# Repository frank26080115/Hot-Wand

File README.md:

# Hot-Wand

This is a handcrafted Metcal RF soldering iron station. It is compact, and powered by USB-C, or a battery, or a DC power supply.

It is compatible with 13.56 MHz handpieces (Metcal, Thermaltronics, Hakko). If the handpiece uses 13.56 MHz and a F-type coaxial connector, then it is compatible.

The project's name, Hot-Wand, reflects how a RF soldering iron feels like magic, and justifies their typical multiple-hundreds-of-dollars price. The spirit of this project is not to lower the price, but to make it portable.

For the light-hearted story of this project, please see [my personal blog post](https://eleccelerator.com/hot-wand-the-rf-soldering-iron/)

The RF circuitry is a derivative of [SergeyMax's design](https://github.com/SergeyMax/SolderingStation), with modifications:

 * redrawn schematic for clarity
 * layout to fit in a Hammond MFG enclosure (or 3D printed enclosure)
 * removed AC power input, uses DC inputs (battery XT30 connector) or USB-PD (with negotiation for 28V)
 * uses a 128x32 OLED display
 * options for low power mode, automatic sleep
 * uses a STM32F042F6P6 microcontroller (more flash memory)
 * cooling fan, temperature sensors
 * internal glass fuse
 * substituted parts that are only available from Russia, or, are otherwise hard to get

I implemented a rather fancy GUI, fancier than what is available on a Metcal soldering station. The firmware features/supports:

 * persistent settings, edited through a setup menu
 * foreground and background power/thermal management
 * low battery warning/cutoff
 * user triggered sleep mode (basically, the power switch)
 * idle detection for automatic sleep
 * various fault detection
 * easter eggs! try and find them

Demo of the power modes:

A key aspect of my design is that it's **easy to build, and to prove it, I built 5 of these in my first batch, and they needed no rework**. All of the lessons and mistakes from the SergeyMax design are accounted for. The files are ready for PCBA assembly service upload and I've optimized the hand assembly to minimize tuning. I want my github repo to be a one-stop-shop of information for anybody who wants to build one.

Actually I built 10, there are 5 of each design, you can see why designing it in a way that doesn't annoy me during the build is important. These are going to be gifts to my BattleBots teammates and friends. The world is stressing everyone out, we could all use some cheering up right now. (can you guess what are our favorite tool brands?)

The circuit board was partially manufactured by a PCBA service, and there are some hand assembly still to be done afterwards. Some of the inductors has to be custom wound.

The USB-C connector is connected to a USB-PD negotiation IC, and the user can choose between using 28V or 20V depending on what USB brick they have. The user can also pick between 3A or 5A but this also depends on the USB cable. There are some tricks (firmware and electrical) being done to make sure the system does not overload the USB-PD host/cable.

The XT30 connector allows the user to connect a battery pack. The user can enable a battery chemistry mode, then features like automatic cell count and low battery cutoff becomes available (the user can also override the cutoff).

The RF power output is through a F-type connector, so it is compatible with most 13.56 MHz handpieces, such as Metcal, Thermaltronics, Hakko.

On paper, the buck converter that is actually powering the RF amplifier is set to 20V output with a 5A current limit. Thinking this means a 80W heat output is optimistic, I would expect somewhere between 50W to 80W of actual heating power, while using up to about 120W total from the upstream. Thus, the highest power setting is meant to be compatible with 140W USB-PD GaN chargers. It does technically work with a 65W USB-PD charger but the experience is a bit degraded.

The buck converter cannot boost the voltage from the input, so using any input voltage below about 22V would mean maximum power cannot be reached. The system cannot function at all below 14V. The DC input is rated for up to a 36V input. There is a glass fuse inside that limits the total system power draw to 7 amps.

While this is a DIY project and not a commercial product, it is a difficult project as it requires hand-wound inductors and tuning the inductor coils. This project is a learning experience, as I had to study the (translated from Russian) blog post made by SergeyMax in detail. See my page on the [design study](./doc/design-study/design-study.md).

## Hot-Wand Lite

In the same spirit, a compact RF soldering iron station. Compatible with 470 kHz handpieces. This is the inexpensive version. It is a derivative of the [Radio Thermal](https://radiothermal.com/) soldering iron station, but with modifications

 * layout to fit in a 3D printed enclosure (but compatible with the Hammond enclosure)
 * uses battery XT30 connector or USB-PD for input
 * uses some sort of Seeed Studio XIAO microcontroller module
 * user selectable power levels via externally pluggable jumpers
 * internal glass fuse

Physically, Hot-Wand and Hot-Wand-Lite uses the same PCB dimensions. The power input stage are almost identical. The RF output connector is a SMA connector this time. [Radio Thermal](https://radiothermal.com/) (the inspiration for this) has instructions on how to build a cheap handpiece.

This cost saving design has way less fault protection.

While this is a DIY project and not a commercial product, it is a difficult project as it requires hand-wound inductors and tuning the inductor coils. Regarding how this is copying a lot of the [Radio Thermal](https://radiothermal.com/) design, I am copying it almost verbatim, as they do not use anything weird from Russia, and the RF design education I've already gotten from the much more complicated 13.56 MHz version of Hot-Wand.

## What is a RF soldering iron anyways?

An RF soldering iron sends high-frequency electromagnetic energy into a purpose-built tip cartridge, where a thin magnetic heating layer produces heat very close to the working end; in Curie-regulated cartridges, that layer also changes how strongly it absorbs energy as it approaches its designed temperature. Compared with a conventional iron whose resistive heater must heat a larger structure and conduct that heat to the tip, the shorter thermal path and low effective thermal lag let an RF tip respond immediately when a solder joint draws heat and recover its temperature quickly afterward. That fast, load-responsive delivery is why a nominally 50 W RF iron can feel more capable than a nominally 100 W resistive iron: the wattage rating describes available electrical power, while the user's experience is dominated by how quickly and efficiently that power reaches the joint and restores the tip temperature.

The RF soldering iron's station unit does not feature a temperature setting or even have the ability to detect the iron's temperature. When you buy the iron cartridge (which is the tip and stem), it is specific to one temperature. It will always be on target (within the manufacture's tolerance) because of the Curie-point behavior of the magnetic alloy built into the cartridge. Below its designed temperature, the alloy is magnetic and the skin effect concentrates RF current in its thin, relatively high-resistance outer layer, producing heat right at the tip. At the Curie point the alloy loses its magnetic properties, the skin effect collapses, and the current moves into the low-resistance copper core, so heating drops sharply. When a solder joint cools the tip, the alloy becomes magnetic again and full heating immediately resumes. The temperature feedback mechanism is therefore inside the heater material itself, directly at the working tip, instead of being a sensor-and-controller loop back in the station.

## Project Ethos

I've always liked the Metcal MX-5200 I have access to at work. I'm also a robot combat competitor, both in insect weight classes and also a part of a heavyweight battlebots team. Thus, I travel with my tools a lot, sometimes even flying to NHRL from California. And while I like my [iFixit soldering iron](https://eleccelerator.com/review-ifixit-soldering-iron/) for it's portability, I thought it'd be cool to have a portable RF soldering iron.

While designing this project, the cost started to balloon. At one point it was decided to drop the pretense that DIY is cheaper, and instead, build something I would rather own even more than the actual (gigantic) MX-5200.

I also wanted to design and document this project in a way that makes it way more friendly for a DIY builder to actually build. To prove myself, the first batch was a batch of 5 and they all worked flawlessly with minimal tuning and zero rework.

Undertaking this project is not cheap, it requires a considerable amount of skill and for you to already have access to soldering equipment. You have been warned. If you need a good soldering iron for a reasonable cost, a Hakko FX-888DX or a iFixit Soldering Iron are still a good bets.

## Design Study

Please see [my full design study (click here)](doc/design-study/design-study.md). This includes:

 * Dissection of SergeyMax's design
 * Analyzes other DIY builder's notes as they build SergeyMax's design
 * Analyzes SergeyMax's follow-up video (that's in Russian)
 * My additional design choices, justifications, calculations
 * and more

See my [post-build report](doc/post-build-report.md) with findings and observations that I've made after completing the project

Please explore the [documentation directory itself](doc), as I might've written something but forgot to link it.

## Files and Build Guides

 * [Electrical Design Files](electrical)
 * [Files for Mechanical Parts](mechanical)
 * [DIY build guide for the Hot Wand (13.56 MHz version)](doc/build-guide-13mhz/build-guide.md)
 * [DIY build guide for the Hot Wand Lite (470 kHz version)](doc/build-guide-lite-470khz/build-guide-lite.md)
 * [Operation Instructions for the Hot Wand (13.56 MHz version)](doc/operating-instructions.md)
 * [Operation Instructions for the Hot Wand Lite (470 kHz version)](doc/operating-instructions-for-lite.md)
 * [DIY build guide for the Folding Iron Stand](doc/build-guide-iron-stand.md)
 * [Interactive Circuit Deep Dive for the Hot Wand (13.56 MHz version)](https://eleccelerator.com/hot-wand-deep-dive/electrical-deep-dive-13mhz.html)
 * [Interactive Circuit Deep Dive for the Hot Wand Lite (470 kHz version)](https://eleccelerator.com/hot-wand-deep-dive/electrical-deep-dive-lite-470khz.html)

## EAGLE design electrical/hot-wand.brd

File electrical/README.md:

This directory contains electrical design files for the Hot Wand project

The main `hot-wand` project is the 13.56 MHz version, while the `hot-wand-lite` is the 470 kHz version meant to be less expensive.

The schematic and PCB are designed with CadSoft EAGLE 7. PDF versions of the schematic and image previews of the PCB are provided for convenience.

 * [Interactive Circuit Deep Dive for the Hot Wand (13.56 MHz version)](https://eleccelerator.com/hot-wand-deep-dive/electrical-deep-dive-13mhz.html)
 * [Interactive Circuit Deep Dive for the Hot Wand Lite (470 kHz version)](https://eleccelerator.com/hot-wand-deep-dive/electrical-deep-dive-lite-470khz.html)

The `mfg` directory will contain the BOM and gerber files, along with some helpers that aid in generating these files.

The BOM, CPL files, and the design rules, are all meant for use with JLCPCB's PCBA service.

## Release Procedure

0. Run a DRU check, and also run `drill_sizes_report.bat` to catch stray drill sizes
1. Edit the symbol and footprint for the version to reflect the latest version designation
2. Generate the schematic preview PDF file using `eagle_schematic_preview.py`
3. Generate the gerber files using `generate_gerbers.bat` (this also generates the gerber preview)
4. Generate the BOM and CPL files using `generate_bom_cpl.bat`

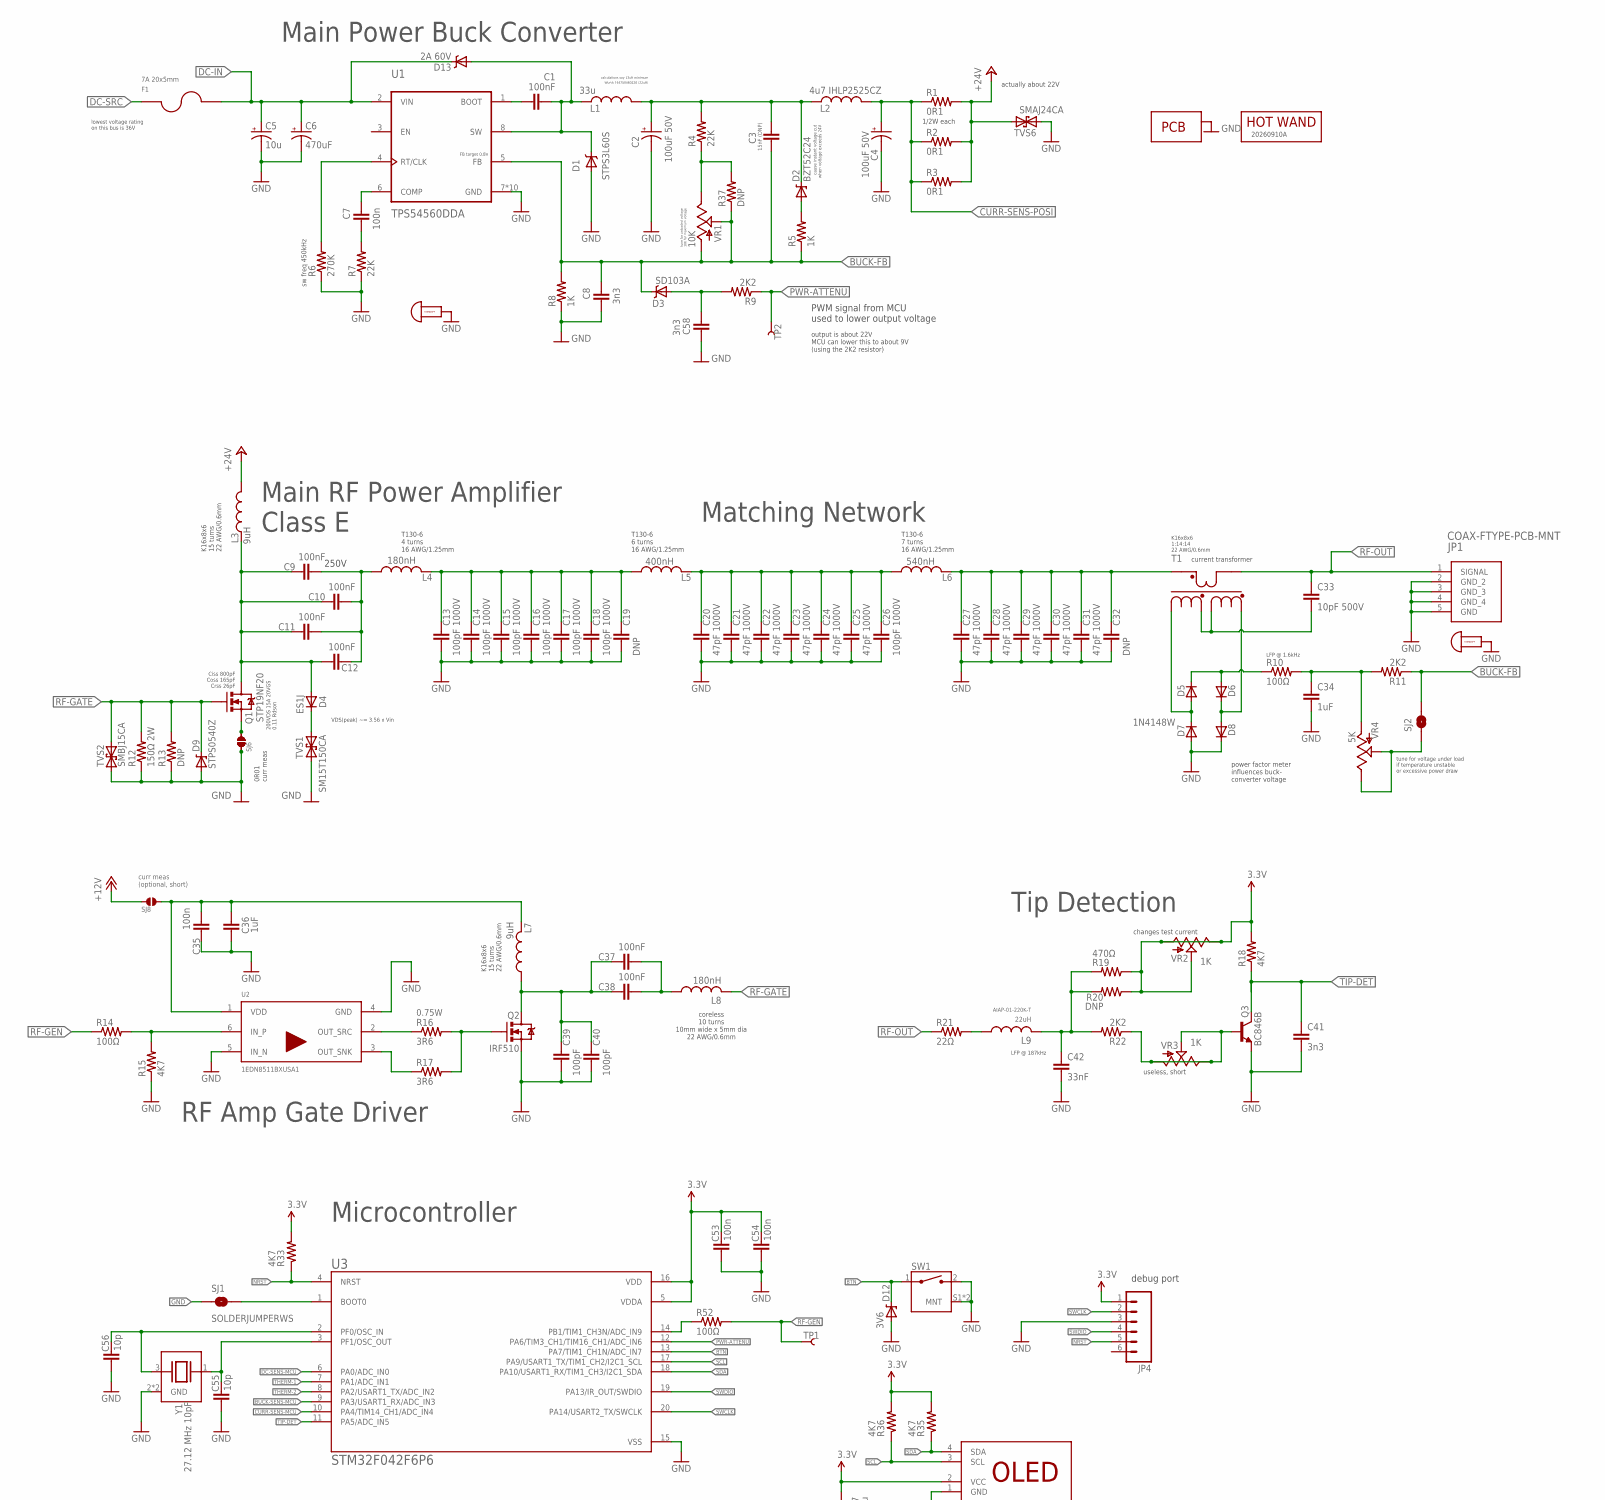
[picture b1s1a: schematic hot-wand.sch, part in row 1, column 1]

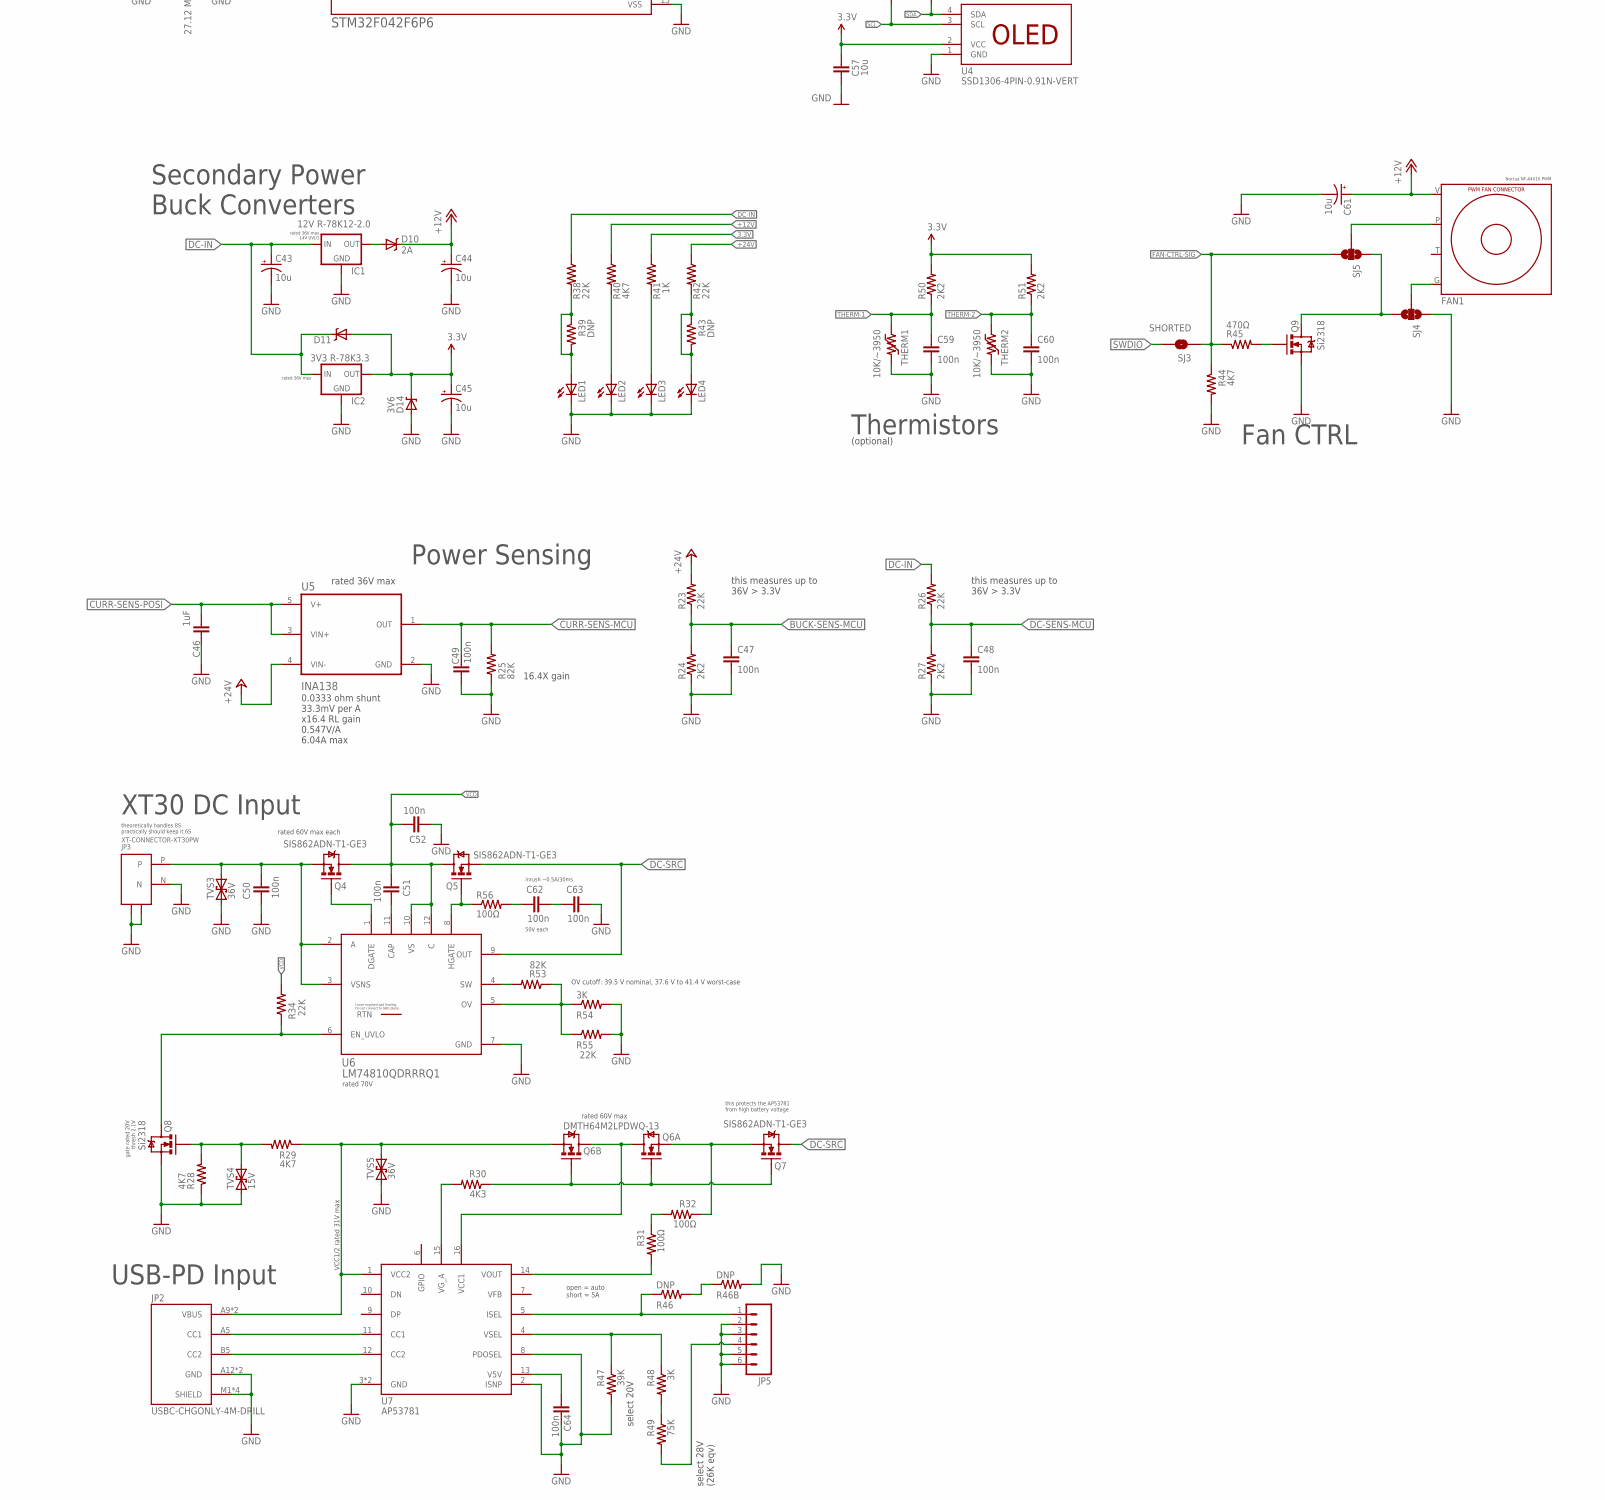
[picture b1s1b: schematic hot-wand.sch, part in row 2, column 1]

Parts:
C1: 100nF; 0603-CAP; JLCPARTNUM C14663
C2: 100uF 50V; CPOL-RADIAL-COMBO-10MM; PARTNUM EEU-FR1H101B;EEU-FR1J101B; JLC-DNP 1
C3: 15nF (DNP); 0805; JLC-DNP 1
C4: 100uF 50V; CPOL-RADIAL-COMBO-10MM; JLC-DNP 1
C5, C43, C61: 10u; EIA3216-KIT; PARTNUM MLASU31LBB5106KTNA01;GRT31CR61H106KE01K; JLCPARTNUM C13585
C6: 470uF; CPOL-RADIAL-1000UF-25V; PARTNUM UHW1H471MPD;EEU-FR1H471;EEU-FR1H471B; JLC-DNP 1
C7, C35, C48, C49, C50, C51, C52, C53, C54, C59, C60, C62, C63, C64: 100n; 0603-CAP; JLCPARTNUM C14663
C8, C41, C58: 3n3; 0603-CAP; JLCPARTNUM C1613
C9, C10, C11, C12, C37, C38: 100nF; 0805-L; PARTNUM CHV0805N250104KXT;MBASQ21GAB7104KTCA01;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; JLCPARTNUM C5182461
C13: 100pF 1000V; 0805-L; PARTNUM QCCT102Q101J1GV001E; JLCPARTNUM C6958299
C14, C15, C16, C17, C18, C26: 100pF 1000V; 0805-L; JLCPARTNUM C6958299
C19: DNP; 0805-L; JLCPARTNUM C6958299
C20: 47pF 1000V; 0805-L; PARTNUM QCCT102Q470J1GV001E; JLCPARTNUM C6366545
C21, C22, C23, C24, C25, C27, C28, C29, C30, C31: 47pF 1000V; 0805-L; JLCPARTNUM C6366545
C32: DNP; 0805-L; JLC-DNP 1
C33: 10pF 500V; 0805-L; PARTNUM QCCT102Q100J1GV001E; JLCPARTNUM C6629873
C34, C36, C46: 1uF; 0603-CAP; JLCPARTNUM C15849
C39, C40: 100pF; 0805-L; JLCPARTNUM C6958299
C42: 33nF; 0603-CAP; JLCPARTNUM C21117
C44: 10u; EIA3216-KIT; PARTNUM TAJA106K016TNJ;T491A106K016AT; JLCPARTNUM C13585
C45: 10u; EIA3216; PARTNUM TAJA106K016TNJ;T491A106K016AT; JLCPARTNUM C13585
C47: 100n; 0603-CAP
C55, C56: 10p; 0603-CAP; JLCPARTNUM C1634
C57: 10u; 1206; JLCPARTNUM C13585
D1: STPS3L60S; SMC; JLCPARTNUM C2971007
D2: BZT52C24; SOD123FL; JLCPARTNUM C2109
D3: SD103A; SOD-323; JLCPARTNUM C7420360
D4: ES1J; SMA-DIODE; JLCPARTNUM C64879
D5, D6, D8: 4148; SOD123FL; JLCPARTNUM C84367
D7: 1N4148W; SOD123FL; JLCPARTNUM C84367
D9: STPS0540Z; SOD123FL; JLCPARTNUM C181835
D10: 2A; SMA-DIODE; PARTNUM VSSAF5N50;SL36A; JLCPARTNUM C698873
D11: DIODE-SCHOTTKY_; SMA-DIODE; JLCPARTNUM C698873
D12, D14: 3V6; SOD-323; PARTNUM ESDLC3V3D3B-TP;CDSOD323-T03SC;SD03LCC; JLCPARTNUM C840638
D13: 2A 60V; SOD123FL; PARTNUM STPS2L60ZFY; JLCPARTNUM C53340922
F1: 7A 20x5mm; FUSE_5MM; PARTNUM Keystone 3518P; JLC-DNP 1
FAN1: FAN-CONN-X4-CONN-X4; FAN-CONN-X4
IC1: 12V R-78K12-2.0; TO220-BUCK-12V; JLC-DNP 1
IC2: 3V3 R-78K3.3; TO220-BUCK-3.3V; JLC-DNP 1
JP1: COAX-FTYPE-PCB-MNT; CONN_73330-0030_MOL; JLC-DNP 1
JP2: USBC-CHGONLY-4M-DRILL; SAMESKY_UJC-H-G-SMT-2-P6-TR-DRILL; JLC-DNP 1
JP3: XT-CONNECTOR-XT30PW; XT30PW; JLC-DNP 1
JP4: M06LOCK; 1X06_LOCK; JLC-DNP 1
JP5: M06LOCK; 1X06_LOCK
L1: 33u; IND_RADIAL_D12.7_COMBO; PARTNUM Wurth 744750460220 (22uH); JLC-DNP 1
L2: 4u7 IHLP2525CZ; IND_IHLP-2525CZ_VIS-M; PARTNUM IHLP2525CZER4R7M11; JLCPARTNUM C845027
L3, L7: 9uH; IND_K16X8X6_X2; JLC-DNP 1
L4: 180nH; IND_T130-6_X2; JLC-DNP 1
L5: 400nH; IND_T130-6_X2; JLC-DNP 1
L6: 540nH; IND_T130-6_X2; JLC-DNP 1
L8: 180nH; IND-10X6MM; JLC-DNP 1
L9: 22uH; TFI0410; PARTNUM AIAP-01-220K-T; JLC-DNP 1
LED1, LED2, LED3, LED4: LED; LED-0603; JLC-DNP 1
PCB1: PCB-OUTLINE; JLC-DNP 1
PCB2: PCB-ART-VERSION; JLC-DNP 1
Q1: STP19NF20; TO220V-REAR; JLC-DNP 1
Q2: IRF510; TO220V-REAR; JLC-DNP 1
Q3: BC846B; SOT23-3; JLCPARTNUM C181138
Q4, Q5, Q7: SIS862ADN-T1-GE3; POWERPAK-1212-8; JLC-DNP 1
Q6: DMTH64M2LPDWQ-13; POWERPAK-SO8-X2; JLC-DNP 1
Q8: Si2318; SOT23-3; PARTNUM 2N7002K;SSM3K388R,LF;Si2318CDS-T1-GE3;P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; JLCPARTNUM C14498;C547263;C5224211;C54347659
Q9: Si2318; SOT23-3; PARTNUM G3404;MMFTN3404A;PJA3404A;Si2318CDS-T1-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; JLCPARTNUM C14498;C547263;C96615
R1, R2, R3: 0R1; 1206; PARTNUM KDV12DR100ET;VMK-R033-1.0-U; JLCPARTNUM C188071
R4, R7, R23, R26, R34, R38, R42, R55: 22K; 0603-RES; JLCPARTNUM C31850
R5, R8, R41: 1K; 0603-RES; JLCPARTNUM C21190
R6: 270K; 0603-RES; JLCPARTNUM C137755
R9, R11, R22, R24, R27, R50, R51: 2K2; 0603-RES; JLCPARTNUM C4190
R10, R14, R52: 100Ω; 0603-RES; JLCPARTNUM C22775
R12: 150Ω 2W; R2512; PARTNUM CRGP2512F150R; JLCPARTNUM C175287
R13: DNP; R2512; PARTNUM CRGP2512F150R; JLC-DNP 1
R15, R18, R28, R29, R33, R35, R36, R40, R44: 4K7; 0603-RES; JLCPARTNUM C23162
R16, R17: 3R6; 1206; JLCPARTNUM C6301221
R19, R45: 470Ω; 0603-RES; JLCPARTNUM C23179
R20: DNP; 0805; JLC-DNP 1
R21: 22Ω; R2512; JLCPARTNUM C5204054
R25, R53: 82K; 0603-RES; JLCPARTNUM C23254
R30: 4K3; 0603-RES; JLCPARTNUM C23159
R31, R32, R56: 100Ω; 0805; JLCPARTNUM C441975
R37, R46, R46B: DNP; 0603-RES; JLC-DNP 1
R39, R43: DNP; 0603-RES
R47: 39K; 0603-RES; JLCPARTNUM C23153
R48, R54: 3K; 0603-RES; JLCPARTNUM C4211
R49: 75K; 0603-RES; JLCPARTNUM C23242
SJ1: SOLDERJUMPERWS; SJ_2S-WS; JLC-DNP 1
SJ2: SOLDERJUMPERNO; SJ_2S-NO; JLC-DNP 1
SJ3: SHORTED; SJ_2S-WS; JLC-DNP 1
SJ4, SJ5: SOLDERJUMPER_2WAYS; SJ_3
SJ6, SJ7, SJ8: SJ-SMALL-1206-SJ; 1206-SJ
STANDOFF1, STANDOFF2: STANDOFF-M2.5-4.5MMHEX
SW1: SW-TACT-SIDE; SW_1-1825027-1; PARTNUM MJTP1236D;TL1105JAF160R1RBLK; JLC-DNP 1
T1: XFORMER-1:14:14; XFORMER-K16X8X6-1:14:14; JLC-DNP 1
THERM1, THERM2: 10K/~3950; 1X02-2MM; PARTNUM B57891M0103K000; JLC-DNP 1
TP1, TP2: TEST-POINT-SQ-2MM; PAD-SQ-2MM
TVS1: SM15T150CA; SMC; JLCPARTNUM C133715
TVS2: SMBJ15CA; SMA-DIODE; JLCPARTNUM C78809
TVS3, TVS5: 36V; SMA; PARTNUM SMAJ36CA; JLCPARTNUM C134984
TVS4: 15V; SOD-323; PARTNUM SD15C-01FTG;CDSOD323-T15SC;TSD15CDYFR; JLCPARTNUM C2987151
TVS6: SMAJ24CA; SMA; JLCPARTNUM C148223
U1: TPS54560DDA; VREG_LM5017MR/NOPB; JLCPARTNUM C31966
U2: 1EDN8511BXUSA1; SOT95P280X145-6N-7-V; JLCPARTNUM C3655509
U3: STM32F042F6P6; SOP65P640X120-20N; JLCPARTNUM C2969989
U4: SSD1306-4PIN-0.91N-VERT; OLED-0.91IN-VERT; JLC-DNP 1
U5: INA138; SOT95P280X145-5N; JLCPARTNUM C47914
U6: LM74810QDRRRQ1; DRR0012E-MFG; JLCPARTNUM C3215601
U7: AP53781; QFN3030-16; JLCPARTNUM C52730979
VR1: 10K; TRIM_35WR1KLFTR_V2; PARTNUM TC33X-2-103E; JLC-DNP 1
VR2, VR3: 1K; TRIM_35WR1KLFTR_V3; PARTNUM TC33X-2-102E; JLC-DNP 1
VR4: 5K; TRIM_35WR1KLFTR_V2; PARTNUM TC33X-2-502; JLC-DNP 1
Y1: 27.12 MHz 10pF; XTAL-4SMD-3.2X2.5-V2; JLCPARTNUM C1986817

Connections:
3.3V: C45.A (+), C53.1, C54.1, C57.2, D11.A, D14.1 (C), IC2.3 (OUT), JP4.1, R18.2, R19.1, R20.1, R33.2, R35.2, R36.2, R41.1, R50.2, R51.2, U3.5 (VDDA), U3.16 (VDD), U4.2 (VCC), VR2.1 (A), VR2.2 (S), VR2.3 (E)
12V-2: D10.A, IC1.3 (OUT)
12V-FOR-GATE-DRIVER: C35.2, C36.2, L7.2, SJ8.2, U2.1 (VDD)
+12V: C44.A (+), C61.A (+), D10.C, FAN1.V, R40.1, SJ8.1
+24V: L3.2, R1.2, R2.2, R3.2, R23.2, R42.1, TVS6.C (2), U5.4 (VIN-)
BTN: D12.1 (C), SW1.1, U3.13 (PA7/TIM1_CH1N/ADC_IN7)
BUCK-1ST-STAGE: C2.1 (+), C2.1B (+), C3.2, D2.C, L1.2, L1.2B (2), L2.1, R4.2
BUCK-FB: C3.1, C8.2, D3.1 (C), R5.1, R8.2, R11.1, R37.1, SJ2.2, U1.5 (FB), VR1.1 (A), VR1.2 (S)
BUCK-SENS-MCU: C47.1, R23.1, R24.2, U3.9 (PA3/USART1_RX/ADC_IN3)
BUCK-SWITCH-NODE: C1.2, D1.C, D13.A, L1.1, L1.1B (1), U1.8 (SW)
CURR-SENS-MCU: C49.1, R25.2, U3.10 (PA4/TIM14_CH1/ADC_IN4), U5.1 (OUT)
CURR-SENS-POSI: C4.1 (+), C4.1B (+), C46.2, L2.2, R1.1, R2.1, R3.1, U5.3 (VIN+), U5.5 (V+)
DC-IN: C5.A (+), C6.1 (+), C43.A (+), D11.C, D13.C, F1.3 (2), F1.4 (2), IC1.1 (IN), IC2.1 (IN), R26.2, R38.1, U1.2 (VIN)
DC-SENS-MCU: C48.1, R26.1, R27.2, U3.6 (PA0/ADC_IN0)
DC-SRC: F1.1, F1.2 (1), Q5.1 (S), Q5.2 (S), Q5.3 (S), Q7.5 (D), Q7.6 (D), Q7.7 (D), Q7.8 (D), Q7.9 (D), U6.9 (OUT)
FAN-CTRL-SIG: R44.1, R45.1, SJ3.1, SJ5.3
GND: C2.2 (-), C2.2B (-), C4.2 (-), C4.2B (-), C5.C (-), C6.2 (-), C8.1, C13.2, C14.2, C15.2, C16.2, C17.2, C18.2, C19.2, C20.2, C21.2, C22.2, C23.2, C24.2, C25.2, C26.2, C27.2, C28.2, C29.2, C30.2, C31.2, C32.2, C34.2, C35.1, C36.1, C39.2, C40.2, C41.2, C42.2, C43.C (-), C44.C (-), C45.C (-), C46.1, C47.2, C48.2, C49.2, C50.2, C52.2, C53.2, C54.2, C55.2, C56.2, C57.1, C58.1, C59.2, C60.2, C61.C (-), C63.1, C64.1, D1.A, D7.A, D8.C, D9.A, D12.2 (A), D14.2 (A), IC1.2 (GND), IC2.2 (GND), JP1.2 (GND_2), JP1.3 (GND_3), JP1.4 (GND_4), JP1.5 (GND), JP2.A12 (GND), JP2.B12 (GND), JP2.M1 (SHIELD), JP2.M2 (SHIELD), JP2.M3 (SHIELD), JP2.M4 (SHIELD), JP3.M1, JP3.M2, JP3.N, JP4.3, JP5.2, JP5.3, JP5.5, JP5.6, LED1.C, LED2.C, LED3.C, LED4.C, PCB1.1, PCB1.2, PCB1.3, PCB1.4, Q2.3 (S), Q3.2 (E), Q8.2 (S), Q9.2 (S), R6.1, R7.1, R8.1, R12.1, R13.1, R15.1, R24.1, R25.1, R27.1, R28.1, R44.2, R46B.2, R47.2, R54.2, R55.2, SJ1.1, SJ4.1, SJ6.1, SJ7.1, STANDOFF1.1, STANDOFF1.2, STANDOFF2.1, STANDOFF2.2, SW1.2, SW1.S1 (MNT), SW1.S2 (MNT), THERM1.2, THERM2.2, TVS1.A (1), TVS2.A (1), TVS3.A (1), TVS4.2 (1), TVS5.A (1), TVS6.A (1), U1.7 (GND), U1.9 (GND), U1.10 (GND), U1.11 (GND), U1.12 (GND), U1.13 (GND), U1.14 (GND), U1.15 (GND), U1.16 (GND), U1.17 (GND), U2.4 (GND), U2.5 (IN_N), U3.15 (VSS), U4.1 (GND), U5.2 (GND), U6.7 (GND), U7.2 (ISNP), U7.3 (GND), U7.8 (PDOSEL), U7.EXP (GND), Y1.2 (GND), Y1.4 (GND)
MCU-BOOT0: SJ1.2, U3.1 (BOOT0)
MCU-OSC-IN: C56.1, U3.2 (PF0/OSC_IN), Y1.3 (2)
MCU-OSC-OUT: C55.1, U3.3 (PF1/OSC_OUT), Y1.1
MCU-RF: R14.2, R15.2, U2.6 (IN_P)
unnamed: L9.1, R21.2
unnamed: C33.2, T1.S1B (4), T1.S2A (3)
unnamed: C20.1, C21.1, C22.1, C23.1, C24.1, C25.1, C26.1, L5.2, L6.1
unnamed: D5.C, D6.A, R10.1
unnamed: D6.C, D8.A, T1.S2B (2)
unnamed: D5.A, D7.C, T1.S1A (1)
unnamed: D4.C, TVS1.C (2)
unnamed: C42.1, L9.2, R19.2, R20.2, R22.2
unnamed: C13.1, C14.1, C15.1, C16.1, C17.1, C18.1, C19.1, L4.2, L5.1
unnamed: C9.2, C10.2, C11.2, C12.2, L4.1
unnamed: R16.1, U2.2 (OUT_SRC)
unnamed: R17.1, U2.3 (OUT_SNK)
unnamed: Q2.1 (G), R16.2, R17.2
unnamed: C37.2, C38.2, L8.1
unnamed: C7.2, U1.6 (COMP)
unnamed: C7.1, R7.2
unnamed: R6.2, U1.4 (RT/CLK)
unnamed: C1.1, U1.1 (BOOT)
unnamed: R4.1, R37.2, VR1.3 (E)
unnamed: D2.A, R5.2
unnamed: C58.2, D3.2 (A), R9.2
unnamed: C62.1, C63.2
unnamed: Q8.1 (G), R28.2, R29.2, TVS4.1 (2)
unnamed: Q6.5 (D), Q6.6 (D), Q6.7 (D), Q6.8 (D), Q6.9 (D), Q6.10 (D), U7.16 (VCC1)
unnamed: C64.2, U7.13 (V5V)
unnamed: R31.2, U7.14 (VOUT)
unnamed: C62.2, R56.2
unnamed: LED2.A, R40.2
unnamed: LED3.A, R41.2
unnamed: LED1.A, R38.2, R39.1, R39.2
unnamed: SJ2.1, VR4.2 (S), VR4.3 (E)
unnamed: Q9.1 (G), R45.2
unnamed: R46.2, R46B.1
unnamed: R31.1, R32.2
unnamed: R48.2, R49.1
unnamed: JP5.4, R49.2
unnamed: LED4.A, R42.2, R43.1, R43.2
unnamed: Q6.1 (S), Q7.1 (S), Q7.2 (S), Q7.3 (S), R32.1
unnamed: FAN1.G, SJ4.2
unnamed: FAN1.P, SJ5.2
unnamed: R53.2, U6.4 (SW)
NRST: JP4.5, R33.1, U3.4 (NRST)
PWR-ATTENU: R9.1, TP2.1, U3.12 (PA6/TIM3_CH1/TIM16_CH1/ADC_IN6)
Q1-VD: C9.1, C10.1, C11.1, C12.1, D4.A, L3.1, Q1.2 (D)
Q1-VS: Q1.3 (S), SJ6.2, SJ7.2
Q2-VD: C37.1, C38.1, C39.1, C40.1, L7.1, Q2.2 (D)
Q3-VB: Q3.1 (B), R22.1, VR3.1 (A), VR3.2 (S), VR3.3 (E)
Q9-VD: Q9.3 (D), SJ4.3, SJ5.1
RF-FB-RECTIFIED: C34.1, R10.2, R11.2, VR4.1 (A)
RF-FINAL: C27.1, C28.1, C29.1, C30.1, C31.1, C32.1, L6.2, T1.P1 (P2)
RF-GATE: D9.C, L8.2, Q1.1 (G), R12.2, R13.2, TVS2.C (2)
RF-GEN: R14.1, R52.2, TP1.1
RF-GEN-: R52.1, U3.14 (PB1/TIM1_CH3N/ADC_IN9)
RF-OUT: C33.1, JP1.1 (SIGNAL), R21.1, T1.P2 (P1)
SCL: R36.1, U3.17 (PA9/USART1_TX/TIM1_CH2/I2C1_SCL), U4.3 (SCL)
SDA: R35.1, U3.18 (PA10/USART1_RX/TIM1_CH3/I2C1_SDA), U4.4 (SDA)
SWCLK: JP4.2, U3.20 (PA14/USART2_TX/SWCLK)
SWDIO: JP4.4, SJ3.2, U3.19 (PA13/IR_OUT/SWDIO)
THERM-1: C59.1, R50.1, THERM1.1, U3.7 (PA1/ADC_IN1)
THERM-2: C60.1, R51.1, THERM2.1, U3.8 (PA2/USART1_TX/ADC_IN2)
TIP-DET: C41.1, Q3.3 (C), R18.1, U3.11 (PA5/ADC_IN5)
U6-CAP: C51.1, U6.11 (CAP)
U6-DGATE: Q4.4 (G), U6.1 (DGATE)
U6-EN: Q8.3 (D), R34.1, U6.6 (EN_UVLO)
U6-HGATE: Q5.4 (G), R56.1, U6.8 (HGATE)
U6-OV: R53.1, R54.1, R55.1, U6.5 (OV)
U7-ISEL: JP5.1, R46.1, U7.5 (ISEL)
U7-VGA: R30.2, U7.15 (VG_A)
U7-VGA-2: Q6.2 (G), Q6.4 (G), Q7.4 (G), R30.1
U7-VSEL: R47.1, R48.1, U7.4 (VSEL)
USB-CC1: JP2.A5 (CC1), U7.11 (CC1)
USB-CC2: JP2.B5 (CC2), U7.12 (CC2)
USB-VBUS: JP2.A9 (VBUS), JP2.B9 (VBUS), Q6.3 (S), R29.1, TVS5.C (2), U7.1 (VCC2)
VCD: C51.2, C52.1, Q4.5 (D), Q4.6 (D), Q4.7 (D), Q4.8 (D), Q4.9 (D), Q5.5 (D), Q5.6 (D), Q5.7 (D), Q5.8 (D), Q5.9 (D), R34.2, U6.10 (VS), U6.12 (C)
VIN-XT30: C50.1, JP3.P, Q4.1 (S), Q4.2 (S), Q4.3 (S), TVS3.C (2), U6.2 (A), U6.3 (VSNS)

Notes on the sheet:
this measures up to 36V > 3.3V
rated 36V max
16.4X gain
0.0333 ohm shunt 33.3mV per A x16.4 RL gain 0.547V/A 6.04A max
Main Power Buck Converter
Power Sensing
RF Amp Gate Driver
Main RF Power Amplifier Class E
current transformer
power factor meter influences buck- converter voltage
Tip Detection
Secondary Power Buck Converters
Matching Network
PWM signal from MCU used to lower output voltage
T130-6 7 turns 16 AWG/1.25mm
T130-6 6 turns 16 AWG/1.25mm
T130-6 4 turns 16 AWG/1.25mm
K16x8x6 1:14:14 22 AWG/0.6mm
K16x8x6 15 turns 22 AWG/0.6mm
coreless 10 turns 10mm wide x 5mm dia 22 AWG/0.6mm
1/2W each
Ciss 800pF Coss 165pF Crss 26pF
200VDS 15A 20VGS 0.11 Rdson
AIAP-01-220K-T
select 20V
XT30 DC Input
USB-PD Input
gate rated 20V thresh 2.1V
Microcontroller
Thermistors
(optional)
LFP @ 1.6kHz
tune for voltage under load if temperature unstable or excessive power draw
useless, short
LFP @ 187kHz
sw freq 450kHz
tune for unloaded voltage 10K for maximum voltage
Wurth 744750460220 (22uH)
output is about 22V MCU can lower this to about 9V (using the 2K2 resistor)
cause instant voltage cut when voltage exceeds 24V

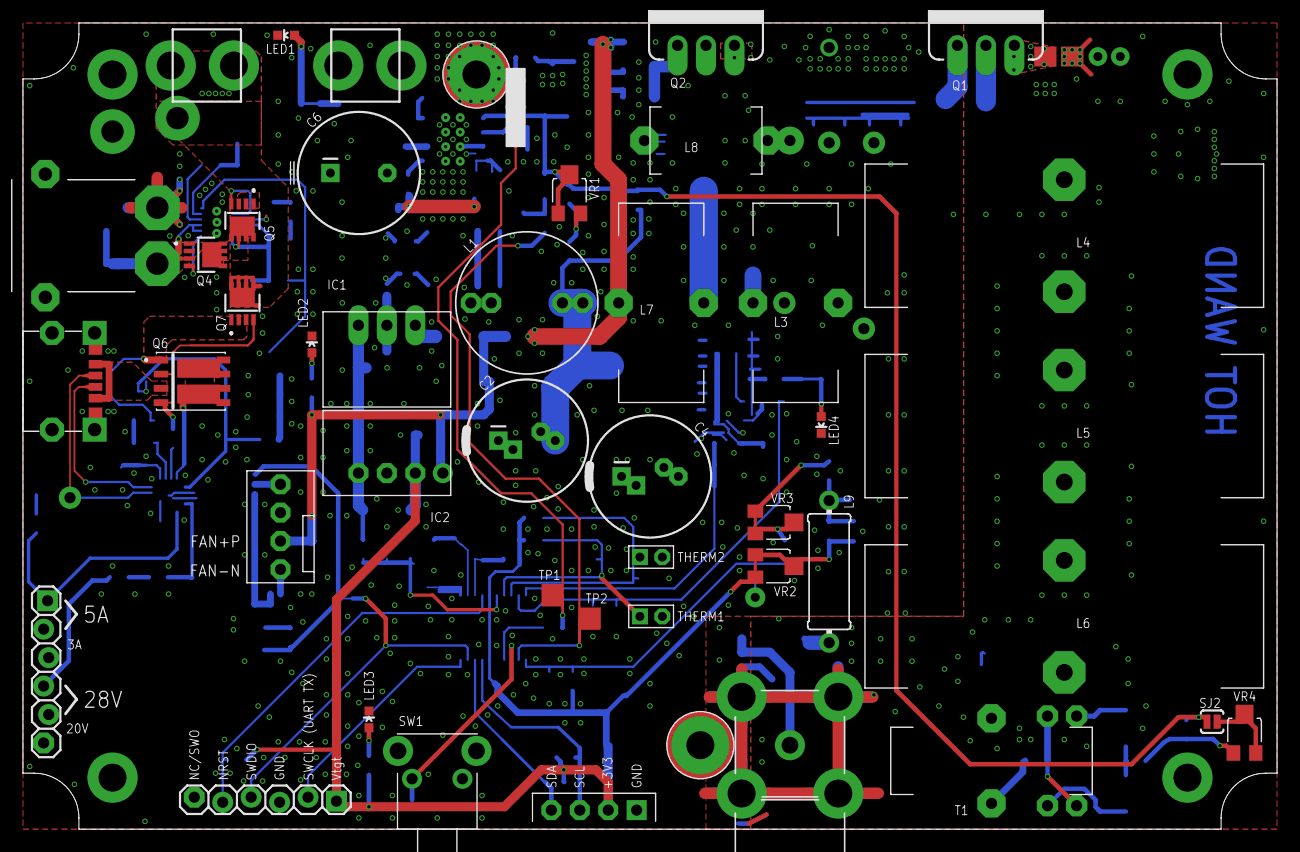
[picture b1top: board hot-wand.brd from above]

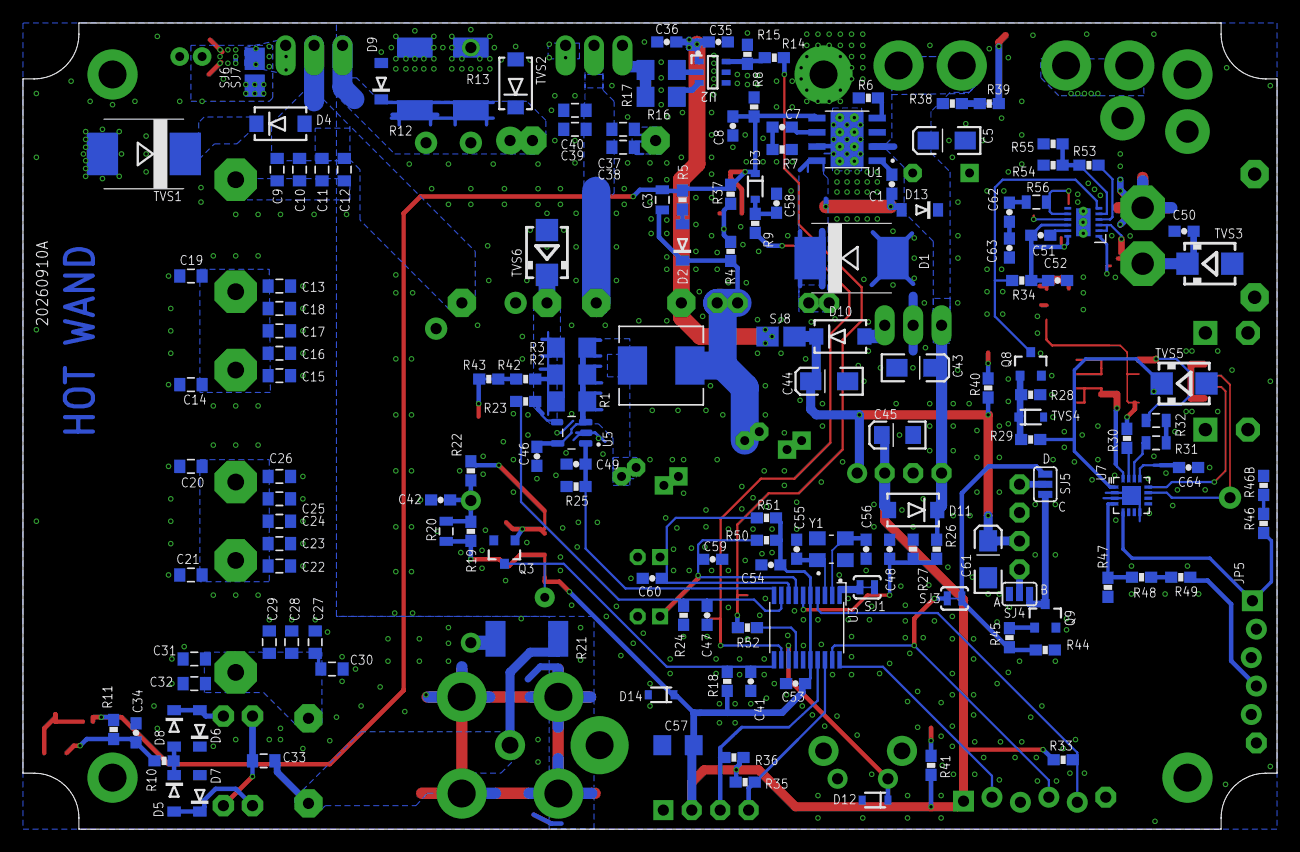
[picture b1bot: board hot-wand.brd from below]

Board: 2 copper layers, 112.0 x 72.0 mm, 202 parts (156 on the bottom side), 96 nets.

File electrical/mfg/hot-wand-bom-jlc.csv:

Comment,Designator,Footprint,LCSC Part #
,JP5,1X06_LOCK,
,D11,SMA-DIODE,C698873
0R1,R1 R2 R3,1206,C188071
1EDN8511BXUSA1,U2,SOT95P280X145-6N-7-V,C3655509
1K,R5 R8 R41,0603-RES,C21190
1N4148W,D7,SOD123FL,C84367
1uF,C34 C36 C46,0603-CAP,C15849
2A,D10,SMA-DIODE,C698873
2A 60V,D13,SOD123FL,C53340922
2K2,R9 R11 R22 R24 R27 R50 R51,0603-RES,C4190
3K,R48 R54,0603-RES,C4211
3R6,R16 R17,1206,C6301221
3V6,D12 D14,SOD-323,C840638
3n3,C8 C41 C58,0603-CAP,C1613
4K3,R30,0603-RES,C23159
4K7,R15 R18 R28 R29 R33 R35 R36 R40 R44,0603-RES,C23162
4u7 IHLP2525CZ,L2,IND_IHLP-2525CZ_VIS-M,C845027
10p,C55 C56,0603-CAP,C1634
10pF 500V,C33,0805-L,C6629873
10u,C57,1206,C13585
10u,C45,EIA3216,C13585
10u,C5 C43 C44 C61,EIA3216-KIT,C13585
15V,TVS4,SOD-323,C2987151
22K,R4 R7 R23 R26 R34 R38 R42 R55,0603-RES,C31850
22,R21,R2512,C5204054
27.12 MHz 10pF,Y1,XTAL-4SMD-3.2X2.5-V2,C1986817
33nF,C42,0603-CAP,C21117
36V,TVS3 TVS5,SMA,C134984
39K,R47,0603-RES,C23153
47pF 1000V,C20 C21 C22 C23 C24 C25 C27 C28 C29 C30 C31,0805-L,C6366545
75K,R49,0603-RES,C23242
82K,R25 R53,0603-RES,C23254
100n,C7 C35 C47 C48 C49 C50 C51 C52 C53 C54 C59 C60 C62 C63 C64,0603-CAP,C14663
100nF,C1,0603-CAP,C14663
100nF,C9 C10 C11 C12 C37 C38,0805-L,C5182461
100pF,C39 C40,0805-L,C6958299
100pF 1000V,C13 C14 C15 C16 C17 C18 C26,0805-L,C6958299
100,R10 R14 R52,0603-RES,C22775
100,R31 R32 R56,0805,C441975
150 2W,R12,R2512,C175287
270K,R6,0603-RES,C137755
470,R19 R45,0603-RES,C23179
4148,D5 D6 D8,SOD123FL,C84367
AP53781,U7,QFN3030-16,C52730979
BC846B,Q3,SOT23-3,C181138
BZT52C24,D2,SOD123FL,C2109
ES1J,D4,SMA-DIODE,C64879
FAN-CONN-X4-CONN-X4,FAN1,FAN-CONN-X4,
INA138,U5,SOT95P280X145-5N,C47914
LM74810QDRRRQ1,U6,DRR0012E-MFG,C3215601
SD103A,D3,SOD-323,C7420360
SM15T150CA,TVS1,SMC,C133715
SMAJ24CA,TVS6,SMA,C148223
SMBJ15CA,TVS2,SMA-DIODE,C78809
STANDOFF-M2.5-4.5MMHEX,STANDOFF1 STANDOFF2,STANDOFF-M2.5-4.5MMHEX,
STM32F042F6P6,U3,SOP65P640X120-20N,C2969989
STPS3L60S,D1,SMC,C2971007
STPS0540Z,D9,SOD123FL,C181835
Si2318,Q8 Q9,SOT23-3,C14498;C547263;C96615
TEST-POINT-SQ-2MM,TP1 TP2,PAD-SQ-2MM,
TPS54560DDA,U1,VREG_LM5017MR/NOPB,C31966

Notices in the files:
parts and their libraries:
COPYRIGHT: Copyright (C) 2026 Ultra Librarian. All rights reserved.
